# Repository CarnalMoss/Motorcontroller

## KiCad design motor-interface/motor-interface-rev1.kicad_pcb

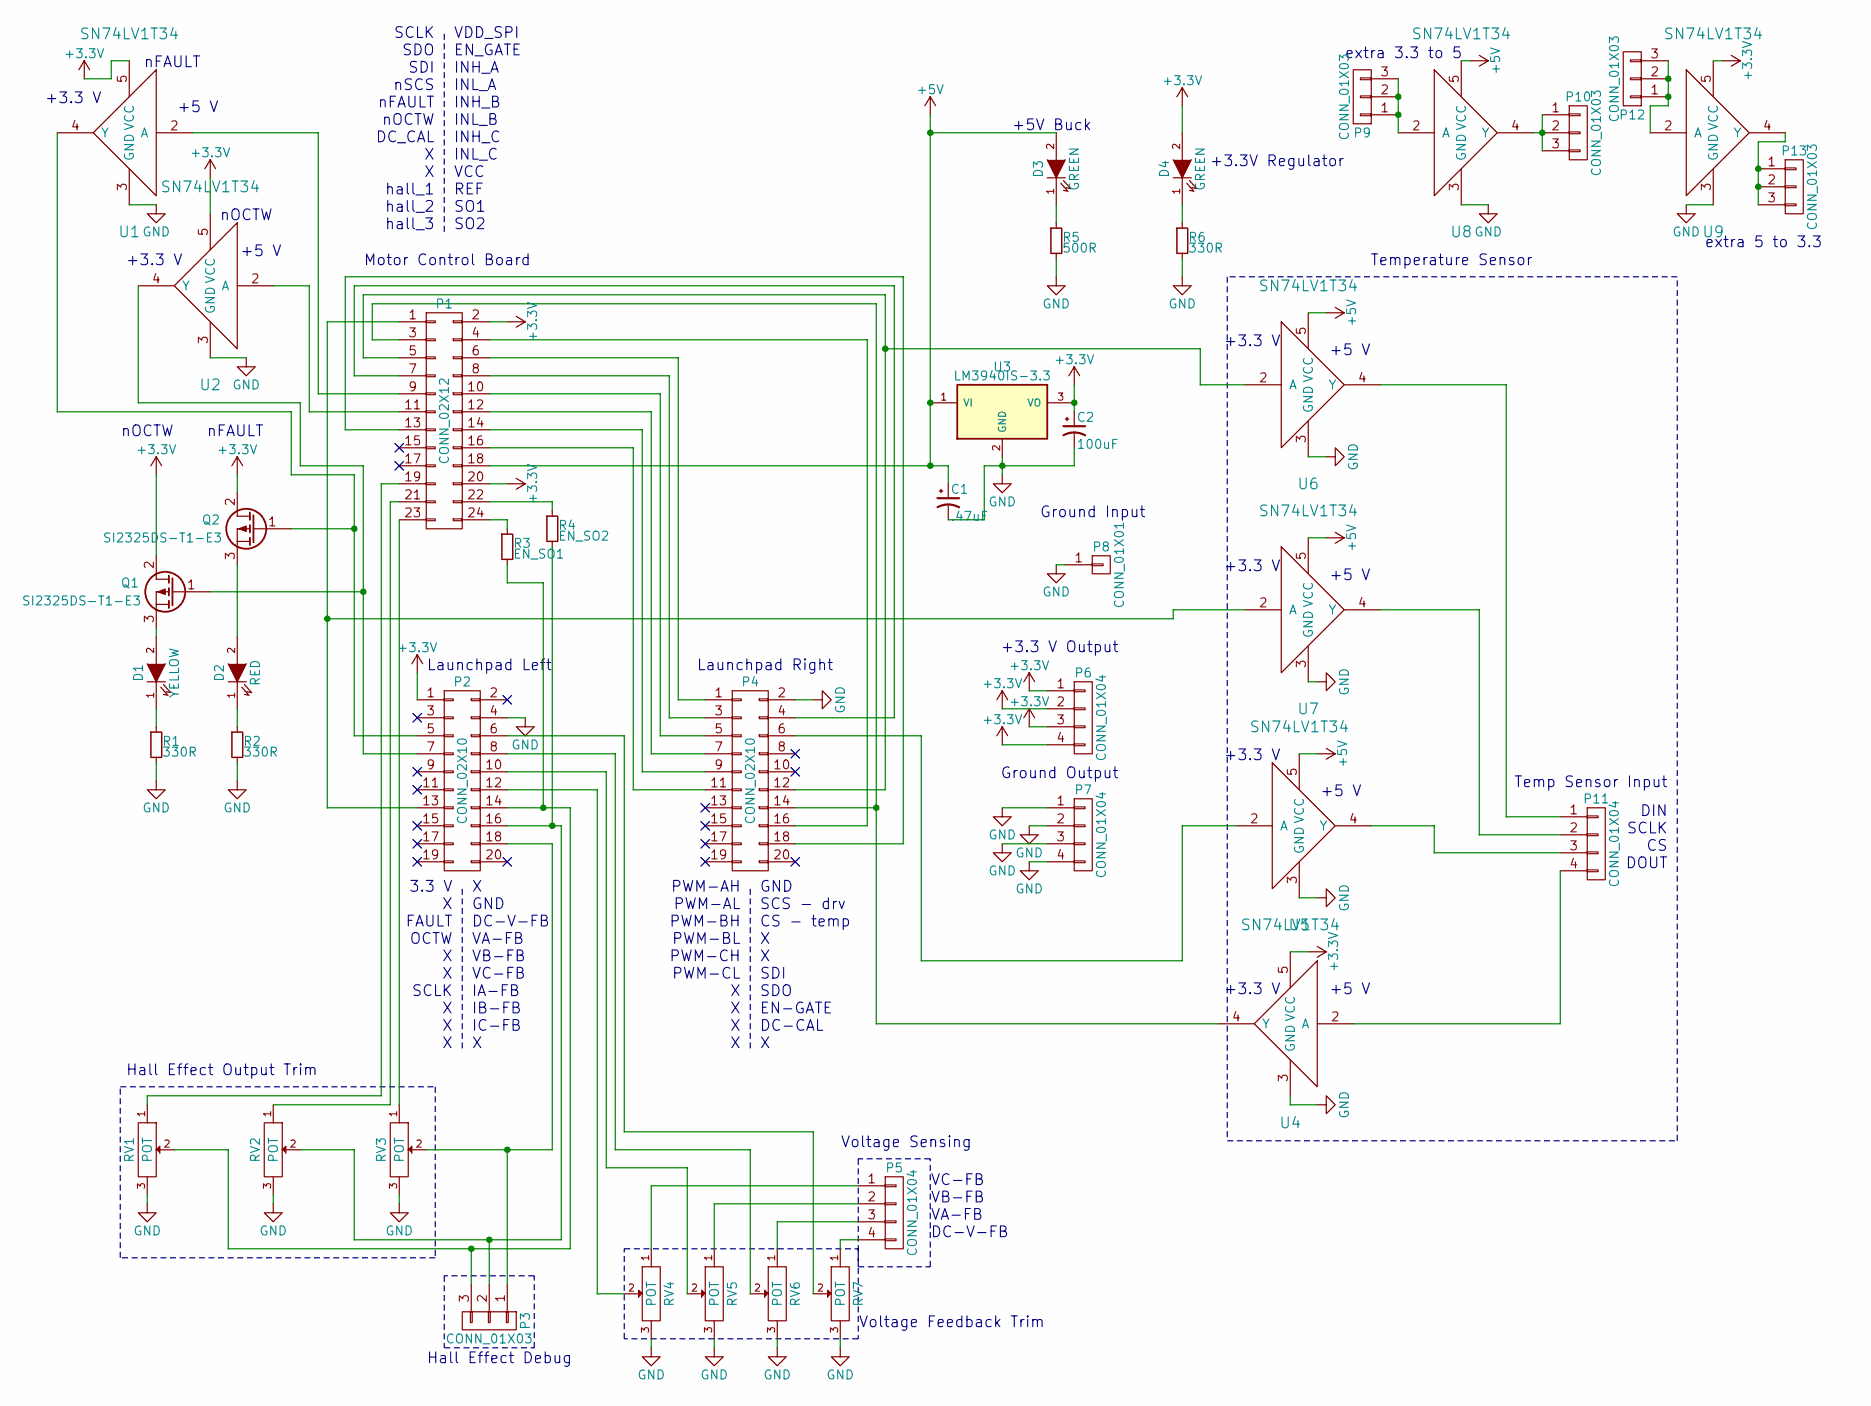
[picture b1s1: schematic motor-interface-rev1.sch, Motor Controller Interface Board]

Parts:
C1: .47uF; TantalC_SizeB_EIA-3528_Reflow
C2: 100uF; TantalC_SizeA_EIA-3216_Reflow
D1: YELLOW; LED-0805
D2: RED; LED-0805
D3, D4: GREEN; LED-0805
P1: CONN_02X12; Pin_Header_Straight_2x12
P2, P4: CONN_02X10; Pin_Header_Straight_2x10
P3, P9, P10, P12, P13: CONN_01X03; Pin_Header_Straight_1x03
P5, P6, P7, P11: CONN_01X04; Pin_Header_Straight_1x04
P8: CONN_01X01; Pin_Header_Straight_1x01
Q1, Q2: SI2325DS-T1-E3
R1, R2, R6: 330R; R_0603
R3: EN_SO1; R_0603
R4: EN_SO2; R_0603
R5: 500R; R_0603
RV1, RV2, RV3, RV4, RV5, RV6, RV7: POT; 3361P
U1, U2, U4, U5, U6, U7, U8, U9: SN74LV1T34
U3: LM3940IS-3.3

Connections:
+3V3: C2.1, D4.2 (A), P1.2, P1.20, P2.1, P6.1, P6.2, P6.3, P6.4, Q1.2 (D), Q2.2 (D), U1.5 (VCC), U2.5 (VCC), U3.3 (VO), U4.5 (VCC), U9.5 (VCC)
+5V: C1.1, D3.2 (A), P1.18, U3.1 (VI), U5.5 (VCC), U6.5 (VCC), U7.5 (VCC), U8.5 (VCC)
GND: C1.2, C2.2, P2.4, P4.2, P7.1, P7.2, P7.3, P7.4, P8.1, R1.2, R2.2, R5.2, R6.2, RV1.3, RV2.3, RV3.3, RV4.3, RV5.3, RV6.3, RV7.3, U1.3 (GND), U2.3 (GND), U3.2 (GND), U4.3 (GND), U5.3 (GND), U6.3 (GND), U7.3 (GND), U8.3 (GND), U9.3 (GND)
unnamed: D1.1 (K), R1.1
unnamed: D1.2 (A), Q1.3 (S)
unnamed: D2.1 (K), R2.1
unnamed: D2.2 (A), Q2.3 (S)
unnamed: D3.1 (K), R5.1
unnamed: D4.1 (K), R6.1
unnamed: P1.1, P2.13, U7.2 (A)
unnamed: P1.3, P4.14, U4.4 (Y)
unnamed: P1.4, P4.16
unnamed: P1.5, P4.12, U6.2 (A)
unnamed: P1.6, P4.1
unnamed: P1.7, P4.4
unnamed: P1.8, P4.3
unnamed: P1.9, U1.2 (A)
unnamed: P1.10, P4.5
unnamed: P1.11, U2.2 (A)
unnamed: P1.12, P4.7
unnamed: P1.13, P4.18
unnamed: P1.14, P4.9
unnamed: P1.16, P4.11
unnamed: P1.19, RV1.1
unnamed: P1.21, RV2.1
unnamed: P1.22, R4.1
unnamed: P1.23, RV3.1
unnamed: P1.24, R3.1
unnamed: P2.5, Q2.1 (G), U1.4 (Y)
unnamed: P2.6, RV7.2
unnamed: P2.7, Q1.1 (G), U2.4 (Y)
unnamed: P2.8, RV6.2
unnamed: P2.10, RV5.2
unnamed: P2.12, RV4.2
unnamed: P2.14, P3.3, R3.2, RV1.2
unnamed: P2.16, P3.2, R4.2, RV2.2
unnamed: P2.18, P3.1, RV3.2
unnamed: P4.6, U5.2 (A)
unnamed: P5.1, RV4.1
unnamed: P5.2, RV5.1
unnamed: P5.3, RV6.1
unnamed: P5.4, RV7.1
unnamed: P9.1, P9.2, P9.3, U8.2 (A)
unnamed: P10.1, P10.2, P10.3, U8.4 (Y)
unnamed: P11.1, U6.4 (Y)
unnamed: P11.2, U7.4 (Y)
unnamed: P11.3, U5.4 (Y)
unnamed: P11.4, U4.2 (A)
unnamed: P12.1, P12.2, P12.3, U9.2 (A)
unnamed: P13.1, P13.2, P13.3, U9.4 (Y)

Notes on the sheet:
X GND DC-V-FB VA-FB VB-FB VC-FB IA-FB IB-FB IC-FB X
3.3 V X FAULT OCTW X X SCLK X X X
GND SCS - drv CS - temp X X SDI SDO EN-GATE DC-CAL X
PWM-AH PWM-AL PWM-BH PWM-BL PWM-CH PWM-CL X X X X
VDD_SPI EN_GATE INH_A INL_A INH_B INL_B INH_C INL_C VCC REF SO1 SO2
SCLK SDO SDI nSCS nFAULT nOCTW DC_CAL X X hall_1 hall_2 hall_3
Ground Input
+3.3 V Output
Ground Output
Temp Sensor Input
DIN SCLK CS DOUT
Temperature Sensor
+3.3 V
+5 V
Hall Effect Output Trim
nOCTW
nFAULT
Hall Effect Debug
Voltage Sensing
VC-FB VB-FB VA-FB DC-V-FB
Voltage Feedback Trim
+5V Buck
+3.3V Regulator
Launchpad Left
Launchpad Right
Motor Control Board
extra 3.3 to 5
extra 5 to 3.3

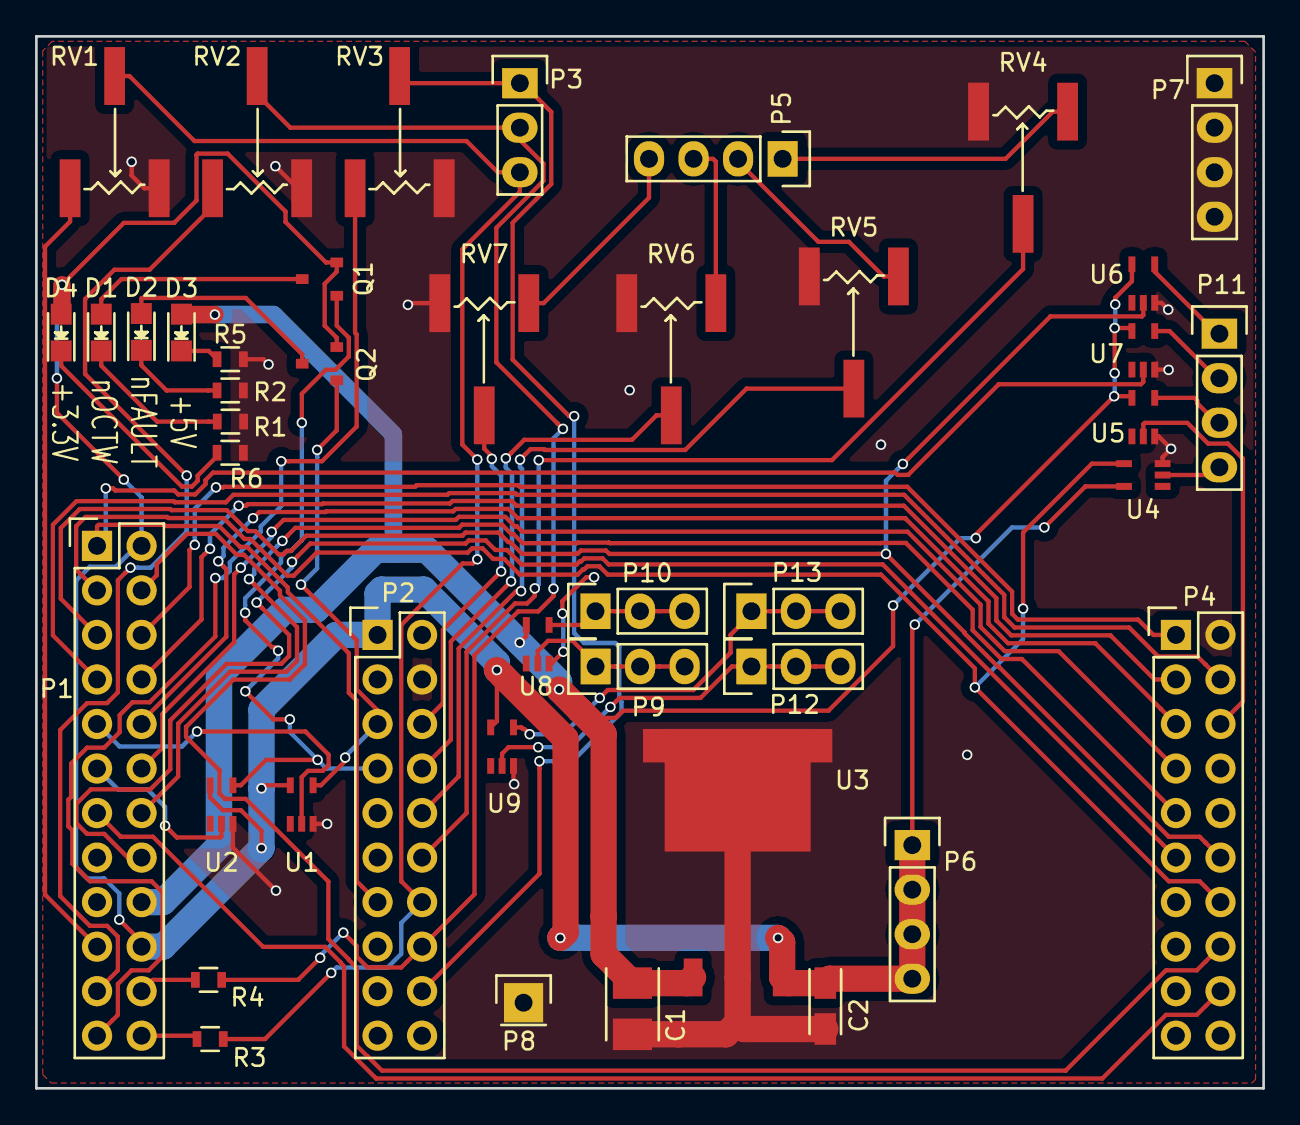
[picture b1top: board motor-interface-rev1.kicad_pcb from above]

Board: 2 copper layers, 70.0 x 60.0 mm, 43 parts (0 on the bottom side), 50 nets.

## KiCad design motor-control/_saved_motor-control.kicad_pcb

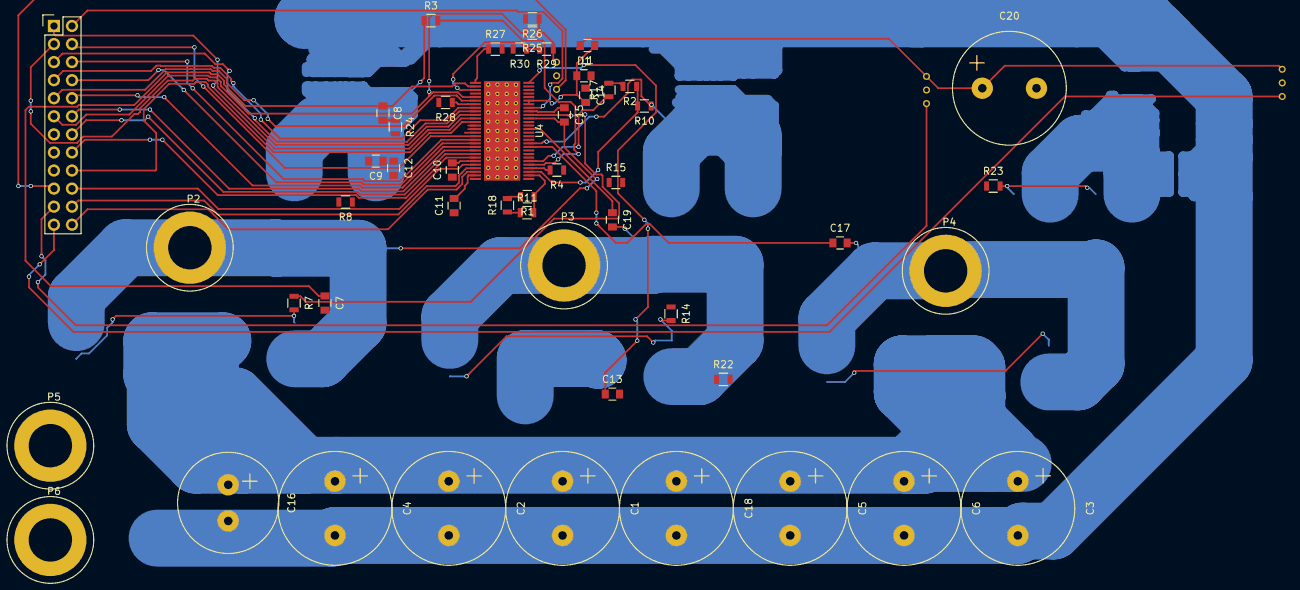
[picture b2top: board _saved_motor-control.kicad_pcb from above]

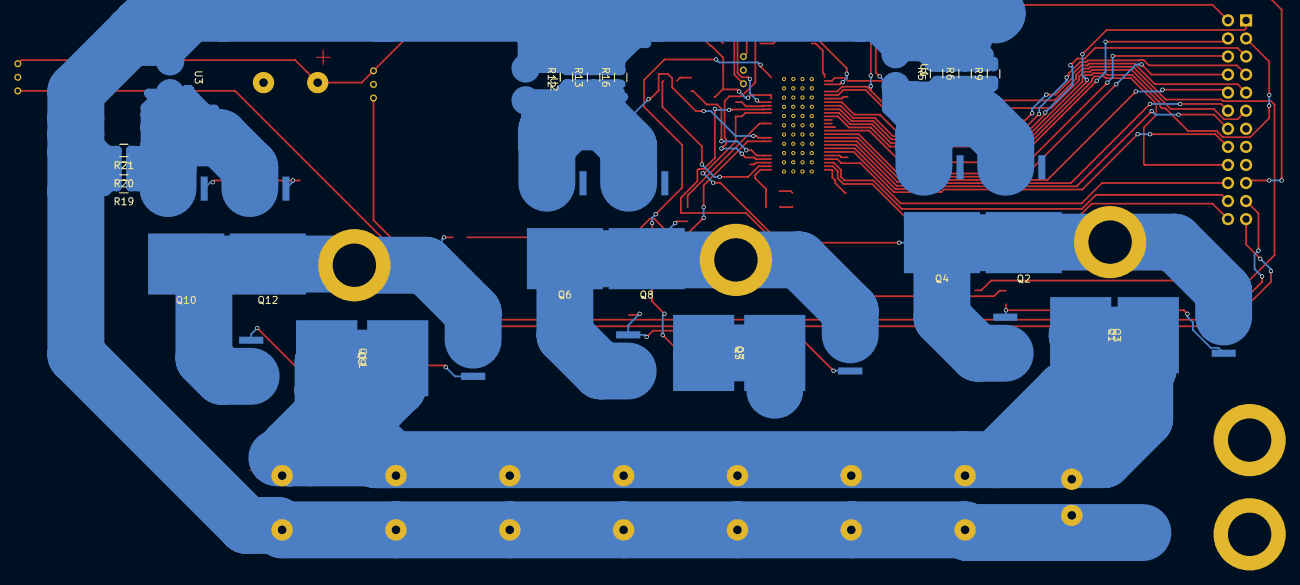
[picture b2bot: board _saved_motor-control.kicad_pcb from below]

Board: 2 copper layers, 74 parts (24 on the bottom side), 64 nets.

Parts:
C1, C2, C3, C4, C5, C6: CP1; Elko_vert_31.5x16mm_RM7.5
C7, C8: C_Small; C_0805
C9: 2.2uF; C_0805
C10, C11: 1uF; C_0805
C12: 0.022uF; C_0805
C13: 0.47nF; C_0805
C14, C15, C17, C19: 0.1uF; C_0805
C16: 0.1uF; Elko_vert_31.5x14mm_RM5
C18: 4.7uF; Elko_vert_31.5x16mm_RM7.5
C20: 47uF; Elko_vert_31.5x16mm_RM7.5
D1: D; C_0805
L1: 22uH; C_0805
P1: CONN_02X12; Pin_Header_Straight_2x12
P2: to_motor_phase_1; Banana_Jack_1Pin
P3: to_motor_phase_2; Banana_Jack_1Pin
P4: to_motor_phase_3; Banana_Jack_1Pin
P5, P6: CONN_01X01; Banana_Jack_1Pin
Q1, Q2, Q3, Q4, Q5, Q6, Q7, Q8, Q9, Q10, Q11, Q12: CSD19536KTT
R1, R2, R28: DNP; R_0805
R3, R4, R10, R11, R17, R18: 0R; R_0805
R5, R6, R9, R12, R13, R16, R19, R20, R21, R24: R; R_0805
R7, R8, R14, R15, R22, R23: 10R; R_0805
R25, R26: 10k; R_0805
R27: 800k; R_0805
R29: 22k; R_0805
R30: 4k; R_0805
U1, U2, U3: ACS770; ACS770xCB
U4: DRV8301

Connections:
+batt: C1.1, C2.1, C3.1, C4.1, C5.1, C6.1, C16.1, C18.1, P5.1, Q1.2, Q3.2, Q5.2, Q7.2, Q9.2, Q11.2, U4.29, U4.53, U4.54
/Gate-Driver/DC_CAL: P1.18, U4.12
/Gate-Driver/EN_GATE: P1.4, U4.16
/Gate-Driver/GH_A: R7.1, U4.47
/Gate-Driver/GH_B: R14.1, U4.42
/Gate-Driver/GH_C: R22.1, U4.37
/Gate-Driver/GL_A: R8.1, U4.45
/Gate-Driver/GL_B: R15.1, U4.40
/Gate-Driver/GL_C: R23.1, U4.35
/Gate-Driver/INH_A: P1.6, U4.17
/Gate-Driver/INH_B: P1.10, U4.19
/Gate-Driver/INH_C: P1.14, U4.21
/Gate-Driver/INL_A: P1.8, U4.18
/Gate-Driver/INL_B: P1.12, U4.20
/Gate-Driver/INL_C: P1.16, U4.22
/Gate-Driver/REF: P1.20, U4.24
/Gate-Driver/S01: P1.22, U4.25
/Gate-Driver/S02: P1.24, U4.26
/Gate-Driver/SCLK: P1.1, U4.11
/Gate-Driver/SDI: P1.5, U4.9
/Gate-Driver/SDO: P1.3, U4.10
/Gate-Driver/SH_A: C15.2, P2.1, Q1.3, Q2.2, Q3.3, Q4.2, U4.46
/Gate-Driver/SH_B: C19.2, P3.1, Q5.3, Q6.2, Q7.3, Q8.2, U4.41
/Gate-Driver/SH_C: C17.2, P4.1, Q9.3, Q10.2, Q11.3, Q12.2, U4.36
/Gate-Driver/SL_A: Q2.3, Q4.3, R3.1, R5.1, R6.1, R9.1, U1.4, U4.44
/Gate-Driver/SL_B: Q6.3, Q8.3, R10.1, R12.1, R13.1, R16.1, U2.4, U4.39
/Gate-Driver/SL_C: Q10.3, Q12.3, R17.1, R19.1, R20.1, R21.1, U3.4, U4.34
/Gate-Driver/SN1: R3.2, U4.33
/Gate-Driver/SN2: R2.1, R10.2, U4.31
/Gate-Driver/SP1: R4.2, U4.32
/Gate-Driver/SP2: R1.1, R11.2, U4.30
/Gate-Driver/VDD_SPI: P1.2, U4.49
/Gate-Driver/nFault: P1.9, R26.2, U4.6
/Gate-Driver/nOCTW: P1.11, R25.2, U4.5
/Gate-Driver/nSCS: P1.7, U4.8
/power mosfets & current sensing/SN3: R2.2, R17.2
/power mosfets & current sensing/SP3: R1.2, R18.2
/power mosfets & current sensing/hall_1: P1.19, U1.3
/power mosfets & current sensing/hall_2: P1.21, U2.3
/power mosfets & current sensing/hall_3: P1.23, U3.3
GND: C1.2, C2.2, C3.2, C4.2, C5.2, C6.2, C7.2, C9.2, C10.1, C11.1, C13.2, C16.2, C18.2, C20.2, D1.2, P6.1, R4.1, R5.2, R6.2, R9.2, R11.1, R12.2, R13.2, R16.2, R18.1, R19.2, R20.2, R21.2, R24.2, R27.2, R28.2, R30.2, U1.5, U2.5, U3.5, U4.28, U4.57
unnamed: C7.1, C8.1, U4.2
unnamed: C8.2, R24.1
unnamed: C9.1, U4.13
unnamed: C10.2, U4.23
unnamed: C11.2, U4.27
unnamed: C12.1, U4.14
unnamed: C12.2, U4.15
unnamed: C13.1, U4.56
unnamed: C14.1, U4.52
unnamed: C14.2, D1.1, L1.1, U4.50, U4.51
unnamed: C15.1, U4.48
unnamed: C17.1, U4.38
unnamed: C19.1, U4.43
unnamed: Q1.1, Q3.1, R7.2
unnamed: Q2.1, Q4.1, R8.2
unnamed: Q5.1, Q7.1, R14.2
unnamed: Q6.1, Q8.1, R15.2
unnamed: Q10.1, Q12.1, R23.2
unnamed: Q9.1, Q11.1, R22.2
unnamed: R27.1, U4.1
unnamed: R28.1, U4.7
unnamed: R29.2, R30.1, U4.3
VCC: C20.1, L1.2, R25.1, R26.1, R29.1, U1.1, U2.1, U3.1

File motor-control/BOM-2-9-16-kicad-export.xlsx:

Reference | Value | Footprint | Voltage | Datasheet
C8 | 0.01uF | Capacitors_SMD:C_0805 |  | http://www.mouser.com/Search/ProductDetail.aspx?R=CC0805KRX7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
C12 | 0.022uF | Capacitors_SMD:C_0805 |  | http://www.mouser.com/Search/ProductDetail.aspx?R=C2012X7R2E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
C23 | 0.047uF | Capacitors_SMD:C_0805 |  | http://www.mouser.com/ProductDetail/AVX/0805YC473KAT2A/?qs=s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
C25 | 0.047uF | Capacitors_SMD:C_0805 |  | http://www.mouser.com/ProductDetail/AVX/0805YC473KAT2A/?qs=s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
C27 | 0.047uF | Capacitors_SMD:C_0805 |  | http://www.mouser.com/ProductDetail/AVX/0805YC473KAT2A/?qs=s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
C14 | 0.1uF | Capacitors_SMD:C_0805 | 10 V
C15 | 0.1uF | Capacitors_SMD:C_0805 | 16 V
C17 | 0.1uF | Capacitors_SMD:C_0805 | 16 V
C19 | 0.1uF | Capacitors_SMD:C_0805 | 16 V
C22 | 0.1uF | Capacitors_SMD:C_0805 |  | http://www.mouser.com/ProductDetail/Kemet/C0805C104K3RACTU/?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
C24 | 0.1uF | Capacitors_SMD:C_0805 |  | http://www.mouser.com/ProductDetail/Kemet/C0805C104K3RACTU/?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
C26 | 0.1uF | Capacitors_SMD:C_0805 |  | http://www.mouser.com/ProductDetail/Kemet/C0805C104K3RACTU/?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
C13 | 0.47nF | Capacitors_SMD:C_0805
C7 | 10pF | Capacitors_SMD:C_0805 |  | http://www.mouser.com/ProductDetail/AVX/04025A100FAT2A/?qs=s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
C18 | 10uF | p16261:FK20X7S2A475K | 100 V | http://www.mouser.com/ProductDetail/TDK/FK20X7S2A475K/?qs=sG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
C10 | 1uF | Capacitors_SMD:C_0805 | 6.3 V | http://www.mouser.com/ProductDetail/TDK/C2012X7S2A105K125AB/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
C11 | 1uF | Capacitors_SMD:C_0805 | 10 V | http://www.mouser.com/ProductDetail/TDK/C2012X7S2A105K125AB/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
C21 | 1uF | Capacitors_SMD:C_0805 | 100 V | http://www.mouser.com/ProductDetail/TDK/C2012X7S2A105K125AB/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
C9 | 2.2uF | Capacitors_SMD:C_0805 | 16 V
C20 | 22uF | Capacitors_SMD:C_0805 | 6.3 V
C1 | 470uF | Capacitors_ThroughHole:C_Radial_D16_L30_P7.5 |  | http://www.digikey.com/product-search/en?keywords=P5850-ND
C2 | 470uF | Capacitors_ThroughHole:C_Radial_D16_L30_P7.5 |  | http://www.digikey.com/product-search/en?keywords=P5850-ND
C3 | 470uF | Capacitors_ThroughHole:C_Radial_D16_L30_P7.5 |  | http://www.digikey.com/product-search/en?keywords=P5850-ND
C4 | 470uF | Capacitors_ThroughHole:C_Radial_D16_L30_P7.5 |  | http://www.digikey.com/product-search/en?keywords=P5850-ND
C5 | 470uF | Capacitors_ThroughHole:C_Radial_D16_L30_P7.5 |  | http://www.digikey.com/product-search/en?keywords=P5850-ND
C6 | 470uF | Capacitors_ThroughHole:C_Radial_D16_L30_P7.5 |  | http://www.digikey.com/product-search/en?keywords=P5850-ND
C16 | DNP | Capacitors_SMD:C_0805 | 100 V
D1 | D | p16261:B220A-13-F |  | http://www.mouser.com/Search/ProductDetail.aspx?R=B220A-13-F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
L1 | 68uH | p16261:PHC-27-683 |  | http://www.coilcraft.com/pdfs/pch.pdf
P5 | CONN_01X01 | Connect:Banana_Jack_1Pin
P6 | CONN_01X01 | Connect:Banana_Jack_1Pin
P7 | CONN_01X04 | Pin_Headers:Pin_Header_Straight_1x04
P1 | CONN_02X12 | Pin_Headers:Pin_Header_Straight_2x12
P2 | to_motor_phase_1 | Connect:Banana_Jack_1Pin
P3 | to_motor_phase_2 | Connect:Banana_Jack_1Pin
P4 | to_motor_phase_3 | Connect:Banana_Jack_1Pin
Q1 | csd19505kcs | p16261:csd19505kcs |  | http://www.mouser.com/ProductDetail/Texas-Instruments/CSD195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
Q10 | csd19505kcs | p16261:csd19505kcs |  | http://www.mouser.com/ProductDetail/Texas-Instruments/CSD195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
Q11 | csd19505kcs | p16261:csd19505kcs |  | http://www.mouser.com/ProductDetail/Texas-Instruments/CSD195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
Q12 | csd19505kcs | p16261:csd19505kcs |  | http://www.mouser.com/ProductDetail/Texas-Instruments/CSD195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
Q2 | csd19505kcs | p16261:csd19505kcs |  | http://www.mouser.com/ProductDetail/Texas-Instruments/CSD195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
Q3 | csd19505kcs | p16261:csd19505kcs |  | http://www.mouser.com/ProductDetail/Texas-Instruments/CSD195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
Q4 | csd19505kcs | p16261:csd19505kcs |  | http://www.mouser.com/ProductDetail/Texas-Instruments/CSD195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
Q5 | csd19505kcs | p16261:csd19505kcs |  | http://www.mouser.com/ProductDetail/Texas-Instruments/CSD195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
Q6 | csd19505kcs | p16261:csd19505kcs |  | http://www.mouser.com/ProductDetail/Texas-Instruments/CSD195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
Q7 | csd19505kcs | p16261:csd19505kcs |  | http://www.mouser.com/ProductDetail/Texas-Instruments/CSD195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
Q8 | csd19505kcs | p16261:csd19505kcs |  | http://www.mouser.com/ProductDetail/Texas-Instruments/CSD195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
Q9 | csd19505kcs | p16261:csd19505kcs |  | http://www.mouser.com/ProductDetail/Texas-Instruments/CSD195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
R12 | .33R | Resistors_ThroughHole:Resistor_Vertical_RM7.5mm |  | http://www.mouser.com/ProductDetail/Yageo/SQP500JB-0R33/?qs=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
R13 | .33R | Resistors_ThroughHole:Resistor_Vertical_RM7.5mm |  | http://www.mouser.com/ProductDetail/Yageo/SQP500JB-0R33/?qs=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
R16 | .33R | Resistors_ThroughHole:Resistor_Vertical_RM7.5mm |  | http://www.mouser.com/ProductDetail/Yageo/SQP500JB-0R33/?qs=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
R19 | .33R | Resistors_ThroughHole:Resistor_Vertical_RM7.5mm |  | http://www.mouser.com/ProductDetail/Yageo/SQP500JB-0R33/?qs=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
R20 | .33R | Resistors_ThroughHole:Resistor_Vertical_RM7.5mm |  | http://www.mouser.com/ProductDetail/Yageo/SQP500JB-0R33/?qs=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
R21 | .33R | Resistors_ThroughHole:Resistor_Vertical_RM7.5mm |  | http://www.mouser.com/ProductDetail/Yageo/SQP500JB-0R33/?qs=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
R5 | .33R | Resistors_ThroughHole:Resistor_Vertical_RM7.5mm |  | http://www.mouser.com/ProductDetail/Yageo/SQP500JB-0R33/?qs=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
R6 | .33R | Resistors_ThroughHole:Resistor_Vertical_RM7.5mm |  | http://www.mouser.com/ProductDetail/Yageo/SQP500JB-0R33/?qs=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
R9 | .33R | Resistors_ThroughHole:Resistor_Vertical_RM7.5mm |  | http://www.mouser.com/ProductDetail/Yageo/SQP500JB-0R33/?qs=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
R10 | 0R | Resistors_SMD:R_0805
R11 | 0R | Resistors_SMD:R_0805
R17 | 0R | Resistors_SMD:R_0805
R18 | 0R | Resistors_SMD:R_0805
R28 | 0R | Resistors_SMD:R_0805 |  | http://www.mouser.com/ProductDetail/Panasonic/ERJ-6GEY0R00V/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
R3 | 0R | Resistors_SMD:R_0805
R4 | 0R | Resistors_SMD:R_0805
R31 | 100R | Resistors_SMD:R_0805 |  | http://www.mouser.com/ProductDetail/Bourns/CRS0805-FX-1000EL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
R32 | 100R | Resistors_SMD:R_0805 |  | http://www.mouser.com/ProductDetail/Bourns/CRS0805-FX-1000EL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
R33 | 100R | Resistors_SMD:R_0805 |  | http://www.mouser.com/ProductDetail/Bourns/CRS0805-FX-1000EL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
R25 | 10k | Resistors_SMD:R_0805 |  | http://www.mouser.com/Search/ProductDetail.aspx?R=CRCW080510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
R26 | 10k | Resistors_SMD:R_0805 |  | http://www.mouser.com/Search/ProductDetail.aspx?R=CRCW080510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
R30 | 10k | Resistors_SMD:R_0805
R14 | 10R | Resistors_SMD:R_0805
R15 | 10R | Resistors_SMD:R_0805
R22 | 10R | Resistors_SMD:R_0805
R23 | 10R | Resistors_SMD:R_0805
R7 | 10R | Resistors_SMD:R_0805
R8 | 10R | Resistors_SMD:R_0805
R27 | 205k | Resistors_SMD:R_0603 |  | http://www.mouser.com/Search/ProductDetail.aspx?R=TNPW060320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
R24 | 24.3k | Resistors_SMD:R_0805
R29 | 53.6k | Resistors_SMD:R_0805
R1 | DNP | Resistors_SMD:R_0805
R2 | DNP | Resistors_SMD:R_0805
U1 | ACS770 | p16261:ACS770xCB |  | http://www.digikey.com/product-search/en?keywords=ACS770LCB-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
U2 | ACS770 | p16261:ACS770xCB |  | http://www.digikey.com/product-search/en?keywords=ACS770LCB-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
U3 | ACS770 | p16261:ACS770xCB |  | http://www.digikey.com/product-search/en?keywords=ACS770LCB-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
U5 | ADT7301 | p16261:ADT7301
U4 | DRV8301 | p16261:DRV8301

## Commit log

2015-10-09 Added schematic and footprint of DRV8301
2015-10-30 Unknown change from a while ago.
2015-10-30 Restructured project, libraries, footprints. pin57
2015-11-01 Actually get rid of deleted files
2015-11-10 Added mosfet to schematic, started making branches
2015-11-10 added mosfets sheet, & driver sheet
2015-11-23 Almost finished gate driver schematic
2015-11-23 Ready for pcb design. Schematic capture seems good
2015-11-23 added hall current/pow-mos ftprnt, schmtc ttl edit
2015-11-23 Annotated schematic & matched footprints
2015-11-24 started the board layout
2015-11-30 more layout changes
2015-12-07 Significant board changes, fixed hall ftpnt
2015-12-07 Made prel design for back, started traces on front
2015-12-08 Started using autorouter push-and-shove
2015-12-08 More changes using autorouter. Finished connector
2015-12-27 started revision 2 of board, changed to thru fets
2015-12-27 Added ftprnts frm kicad, other rev2 files
2015-12-28 Just trying to get things together
2015-12-29 Rough design minus power and ground fills done
2016-01-06 Added VCC in shematic
2016-01-06 Added temp sensor ADT7301 sot-23
2016-01-07 Modified power layout extensively, moved vcc pin
2016-01-07 Added power ground and power traces
2016-01-07 Changing the non-power stuff
2016-01-09 More traces done on the digital side
2016-01-09 More changes
2016-01-09 Moved in all components, need last traces and GND
2016-01-09 All components in place, now to fix it up
2016-01-19 Stuff I didn't commit from last time
2016-01-19 Added Top Solder mask layer, redrew gnd plane
2016-01-19 Added bottom solder mask layer
2016-01-19 Redid board edge, increase copper&mask plane dist
2016-01-19 Almost! Added digital gnd, & connected some gnds
2016-01-20 Silkscreen round 1: oriented labels
2016-01-20 Added dimensions & wire jumper #s
2016-01-22 Modified Schematic Comp resist/cap vals, added bom
2016-01-23 Added some datasheet links, additional RC values
2016-01-28 Updated BOM
2016-02-02 Modified hall footprint, began replacement in pcb
2016-02-02 Started Spacing the fets
2016-02-02 Continued FET movement and spacing 1st reg good
2016-02-03 Connected grounds, moved temp sensor, some silk
2016-02-03 Moved a batt pin up left, began right hall fixes
2016-02-04 Finished right side mosfet separation
2016-02-04 Added hall filtering/bypass, part #s, associations
2016-02-04 Added hall filtering components to pcb
2016-02-04 Began rework bottom fets spacing
2016-02-04 Cont. work on bottom fets, fixed a no conn. on drv
2016-02-04 Continued work on bottom fets. Fixed a zone on top
2016-02-04 Finished up bottom fets
2016-02-04 Chnaged schematic buck values according to TI
2016-02-04 Added values in schematic, new diode&induct ftpnts
2016-02-05 Updated pcb diode and inductor, placed them
2016-02-05 rid bad 3d, add new cap thruhole, add datasht lnks
2016-02-08 Fixd*1 ground(hall): added trace to other hall gnd
2016-02-08 Power FETs spaced apart without fixing it up
2016-02-09 fixd bottm sect trans spacing, upped via 1.7x1.016
2016-02-09 Top fets spacing & vias fixed
2016-02-09 Finished right side fets & vias
2016-02-09 Sized up hopefully all conn. vias to 1.7/1.016mm
2016-02-09 added front soldermask to all connecting vias
2016-02-09 Added four mounting holes
2016-02-09 Slightly moved hall up, moved fab text, some silk
2016-02-09 Added back silk credits. may be error w/ proj.file
2016-02-09 fixed error where conn via 7 hit +batt
2016-02-09 Don't know
2016-02-10 Added BOM file
2016-02-10 Unknown changes, maybe as result of plotting gerbe
2016-02-18 rem vcc via, cng via size, fxd drc except internal
2016-02-19 updated drv8301 via. sent design state to advanced
2016-03-21 Started Work on interface auxiliary board
2016-03-22 Done with 1st pass of interface board schematic
2016-03-22 Performed annotation, added 2 missing gnds
2016-03-22 Added BOM files
2016-03-30 Added 3.3V conn to launch, added pots&volt.sensing
2016-04-01 newftprnts,ftprntassoc.bckup3.3to5v,etc
2016-04-02 Created board outline
2016-04-02 Added keepouts, progress on layout
2016-04-02 Added new net file and rescue lib file
2016-04-03 Finished inital track laying. still need gnd fill
2016-04-03 put in fills, moved f.fab, all connections made
2016-04-03 Added some datasheet links for completeness
2018-02-16 First attempt at pushing repo
